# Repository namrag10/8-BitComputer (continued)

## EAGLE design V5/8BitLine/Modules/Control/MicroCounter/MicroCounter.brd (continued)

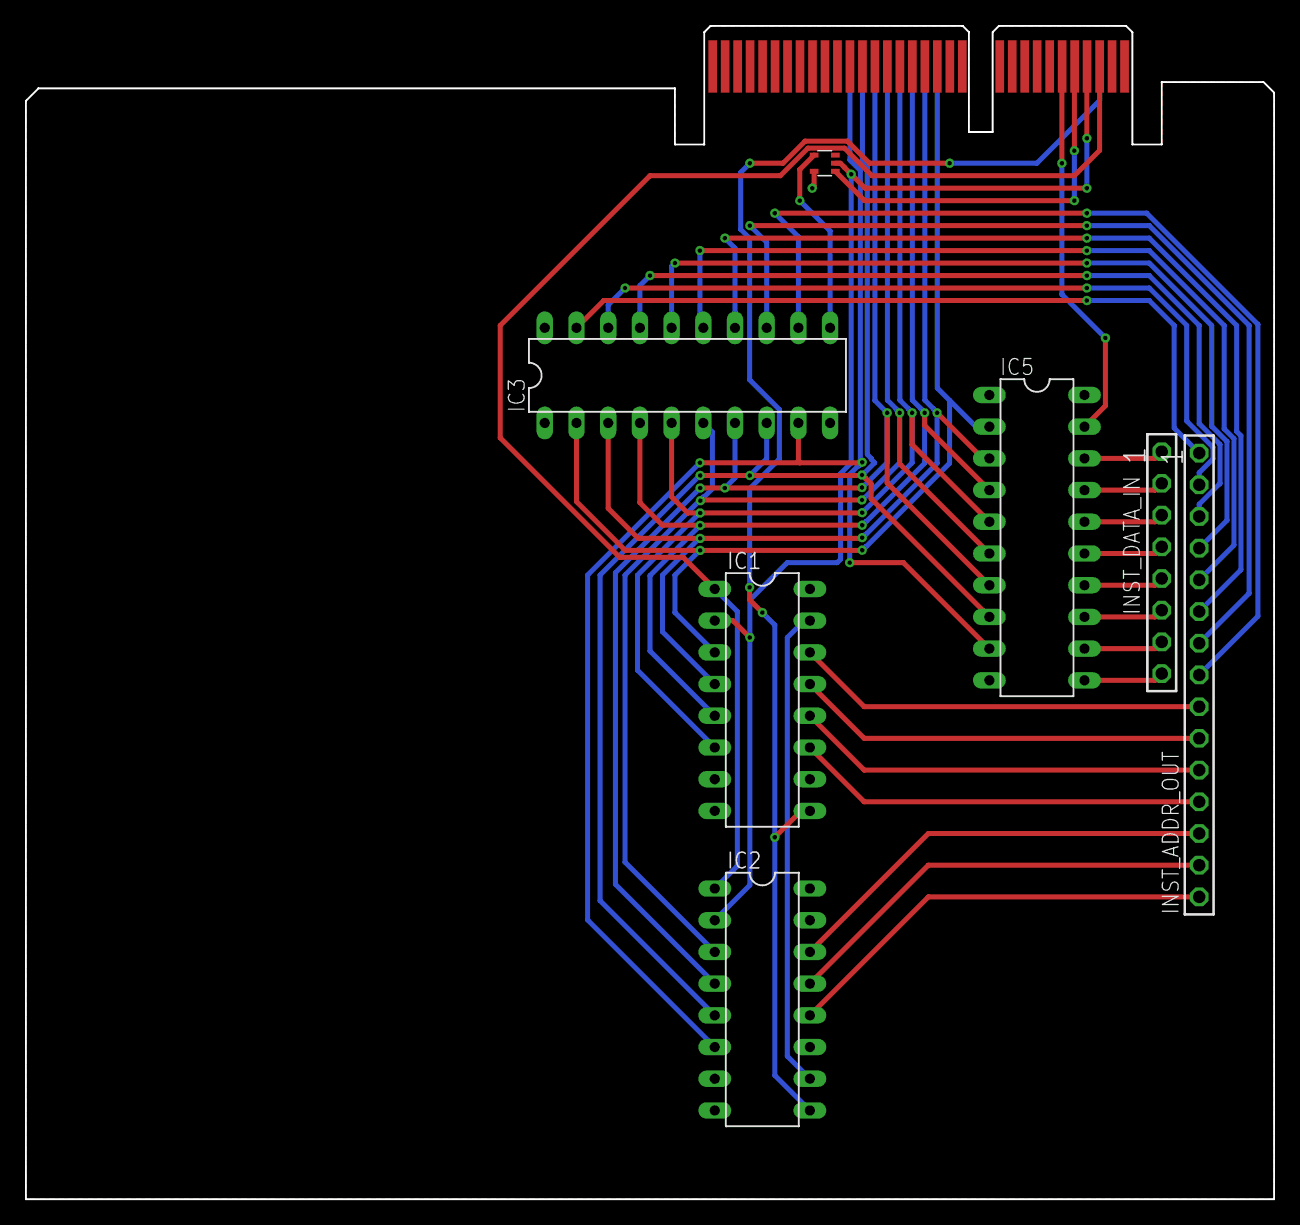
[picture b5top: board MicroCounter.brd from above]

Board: 2 copper layers, 100.0 x 94.0 mm, 8 parts (0 on the bottom side), 40 nets.

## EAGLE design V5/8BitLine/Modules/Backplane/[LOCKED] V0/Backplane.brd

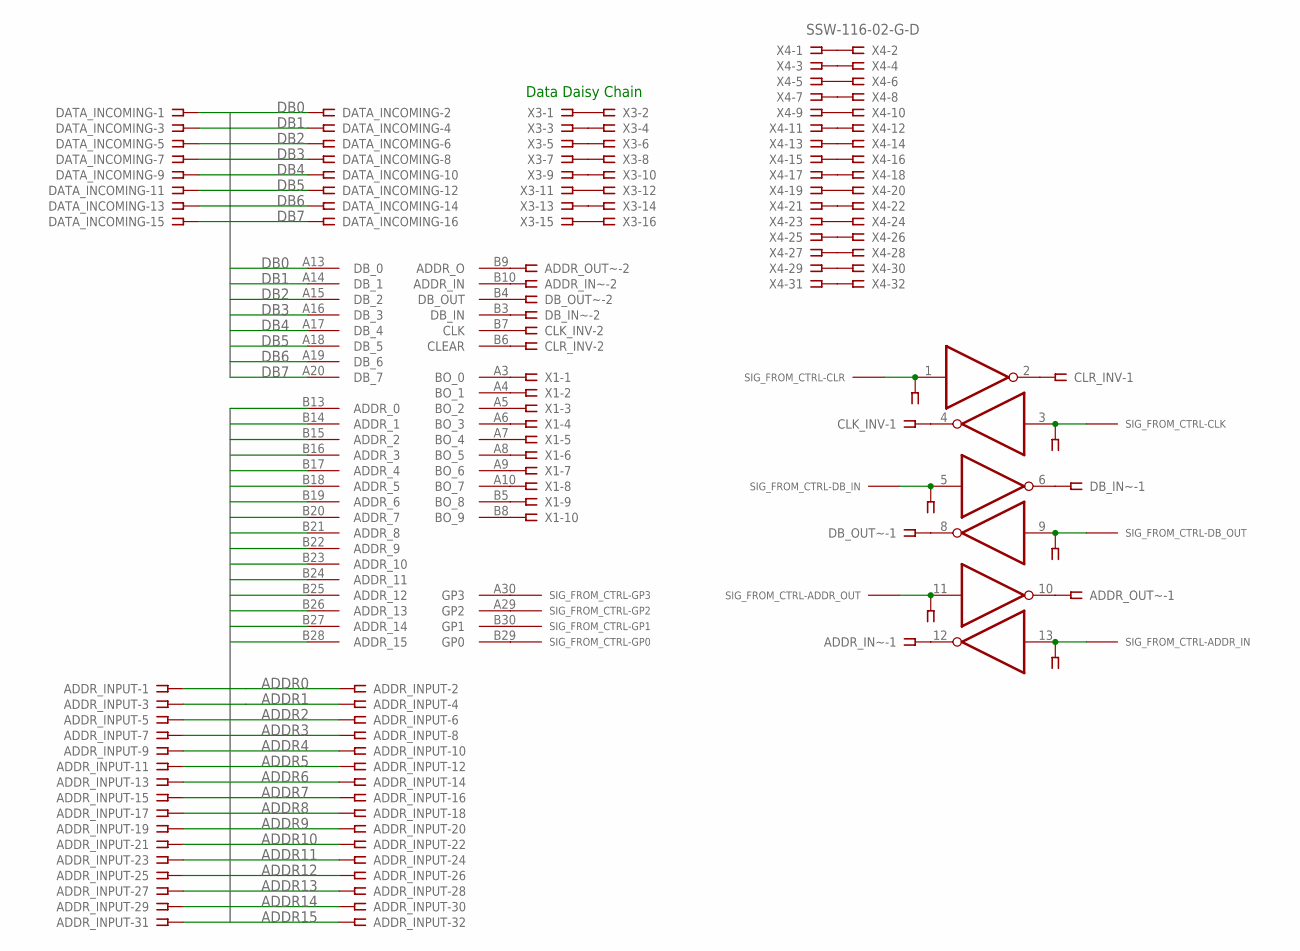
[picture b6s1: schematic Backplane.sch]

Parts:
ADDR_INPUT: SSW-116-02-G-D
ADDR_IN~: SSW-103-02-G-S
ADDR_OUT~: SSW-103-02-G-S
CLK_INV: SSW-103-02-G-S
CLR_INV: SSW-103-02-G-S
DATA_INCOMING: SSW-108-02-G-D
DB_IN~: SSW-103-02-G-S
DB_OUT~: SSW-103-02-G-S
IC1: 74AC04N; DIL14
SIG_FROM_CTRL-: CONTROL_SIG-INT; CONTROL_SIG-INT-FOOT
U$2: BACKPLATE_INTERFACEHEADER; PCI_INTERFACE
X1: SSW-105-02-G-D
X3: SSW-108-02-G-D
X4: SSW-116-02-G-D

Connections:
ADDR0: ADDR_INPUT.1, ADDR_INPUT.2, U$2.B13 (ADDR_0)
ADDR1: ADDR_INPUT.3, ADDR_INPUT.4, U$2.B14 (ADDR_1)
ADDR2: ADDR_INPUT.5, ADDR_INPUT.6, U$2.B15 (ADDR_2)
ADDR3: ADDR_INPUT.7, ADDR_INPUT.8, U$2.B16 (ADDR_3)
ADDR4: ADDR_INPUT.9, ADDR_INPUT.10, U$2.B17 (ADDR_4)
ADDR5: ADDR_INPUT.11, ADDR_INPUT.12, U$2.B18 (ADDR_5)
ADDR6: ADDR_INPUT.13, ADDR_INPUT.14, U$2.B19 (ADDR_6)
ADDR7: ADDR_INPUT.15, ADDR_INPUT.16, U$2.B20 (ADDR_7)
ADDR8: ADDR_INPUT.17, ADDR_INPUT.18, U$2.B21 (ADDR_8)
ADDR9: ADDR_INPUT.19, ADDR_INPUT.20, U$2.B22 (ADDR_9)
ADDR10: ADDR_INPUT.21, ADDR_INPUT.22, U$2.B23 (ADDR_10)
ADDR11: ADDR_INPUT.23, ADDR_INPUT.24, U$2.B24 (ADDR_11)
ADDR12: ADDR_INPUT.25, ADDR_INPUT.26, U$2.B25 (ADDR_12)
ADDR13: ADDR_INPUT.27, ADDR_INPUT.28, U$2.B26 (ADDR_13)
ADDR14: ADDR_INPUT.29, ADDR_INPUT.30, U$2.B27 (ADDR_14)
ADDR15: ADDR_INPUT.31, ADDR_INPUT.32, U$2.B28 (ADDR_15)
DB0: DATA_INCOMING.1, DATA_INCOMING.2, U$2.A13 (DB_0)
DB1: DATA_INCOMING.3, DATA_INCOMING.4, U$2.A14 (DB_1)
DB2: DATA_INCOMING.5, DATA_INCOMING.6, U$2.A15 (DB_2)
DB3: DATA_INCOMING.7, DATA_INCOMING.8, U$2.A16 (DB_3)
DB4: DATA_INCOMING.9, DATA_INCOMING.10, U$2.A17 (DB_4)
DB5: DATA_INCOMING.11, DATA_INCOMING.12, U$2.A18 (DB_5)
DB6: DATA_INCOMING.13, DATA_INCOMING.14, U$2.A19 (DB_6)
DB7: DATA_INCOMING.15, DATA_INCOMING.16, U$2.A20 (DB_7)
GND: IC1.7 (GND), SIG_FROM_CTRL-.GND, U$2.B2 (GND), U$2.B31 (GND)
unnamed: CLR_INV.2, U$2.B6 (CLEAR)
unnamed: CLR_INV.3, IC1.1 (I), SIG_FROM_CTRL-.CLR (0)
unnamed: CLK_INV.2, U$2.B7 (CLK)
unnamed: DB_IN~.2, U$2.B3 (DB_IN)
unnamed: DB_OUT~.2, U$2.B4 (DB_OUT)
unnamed: SIG_FROM_CTRL-.GP0 (0), U$2.B29 (GP0)
unnamed: SIG_FROM_CTRL-.GP1 (0), U$2.B30 (GP1)
unnamed: CLK_INV.3, IC1.3 (I), SIG_FROM_CTRL-.CLK (0)
unnamed: DB_IN~.3, IC1.5 (I), SIG_FROM_CTRL-.DB_IN (0)
unnamed: DB_OUT~.3, IC1.9 (I), SIG_FROM_CTRL-.DB_OUT (0)
unnamed: SIG_FROM_CTRL-.GP2 (0), U$2.A29 (GP2)
unnamed: SIG_FROM_CTRL-.GP3 (0), U$2.A30 (GP3)
unnamed: ADDR_OUT~.3, IC1.11 (I), SIG_FROM_CTRL-.ADDR_OT (0)
unnamed: ADDR_OUT~.1, IC1.10 (O)
unnamed: CLR_INV.1, IC1.2 (O)
unnamed: CLK_INV.1, IC1.4 (O)
unnamed: DB_IN~.1, IC1.6 (O)
unnamed: DB_OUT~.1, IC1.8 (O)
unnamed: ADDR_IN~.3, IC1.13 (I), SIG_FROM_CTRL-.ADDR_IN (0)
unnamed: ADDR_IN~.1, IC1.12 (O)
unnamed: ADDR_OUT~.2, U$2.B9 (ADDR_O)
unnamed: ADDR_IN~.2, U$2.B10 (ADDR_IN)
unnamed: U$2.A3 (BO_0), X1.1
unnamed: U$2.A4 (BO_1), X1.2
unnamed: U$2.A5 (BO_2), X1.3
unnamed: U$2.A6 (BO_3), X1.4
unnamed: U$2.A7 (BO_4), X1.5
unnamed: U$2.A8 (BO_5), X1.6
unnamed: U$2.A9 (BO_6), X1.7
unnamed: U$2.A10 (BO_7), X1.8
unnamed: U$2.B5 (BO_8), X1.9
unnamed: U$2.B8 (BO_9), X1.10
unnamed: X3.1, X3.2
unnamed: X3.3, X3.4
unnamed: X3.5, X3.6
unnamed: X3.7, X3.8
unnamed: X3.9, X3.10
unnamed: X3.11, X3.12
unnamed: X3.13, X3.14
unnamed: X3.15, X3.16
unnamed: X4.1, X4.2
unnamed: X4.3, X4.4
unnamed: X4.5, X4.6
unnamed: X4.7, X4.8
unnamed: X4.9, X4.10
unnamed: X4.11, X4.12
unnamed: X4.13, X4.14
unnamed: X4.15, X4.16
unnamed: X4.17, X4.18
unnamed: X4.19, X4.20
unnamed: X4.21, X4.22
unnamed: X4.23, X4.24
unnamed: X4.25, X4.26
unnamed: X4.27, X4.28
unnamed: X4.29, X4.30
unnamed: X4.31, X4.32
VCC: IC1.14 (VCC), SIG_FROM_CTRL-.VCC, U$2.A2 (VCC), U$2.A31 (VCC)

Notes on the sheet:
Data Daisy Chain

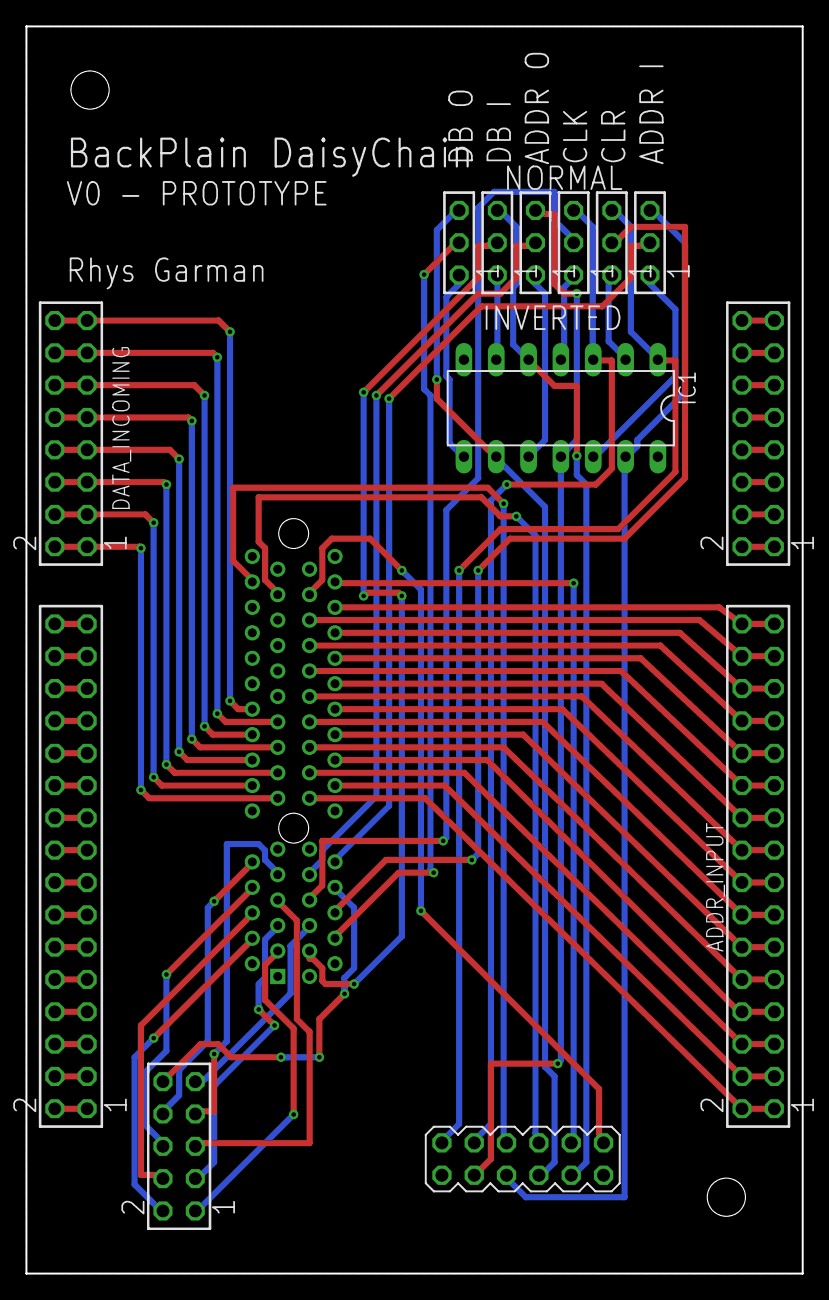
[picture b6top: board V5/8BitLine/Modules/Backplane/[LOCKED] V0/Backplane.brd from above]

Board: 2 copper layers, 61.0 x 98.0 mm, 14 parts (0 on the bottom side), 82 nets.

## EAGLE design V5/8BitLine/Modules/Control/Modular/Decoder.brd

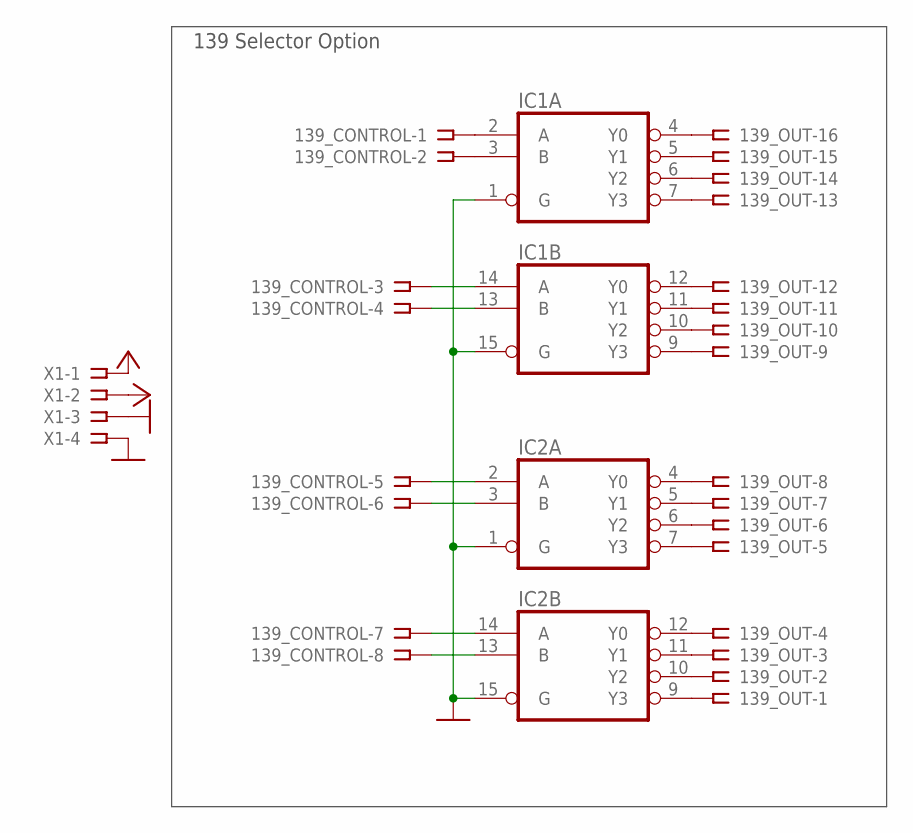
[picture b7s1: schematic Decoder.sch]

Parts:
139_CONTROL: SSW-108-02-G-S
139_OUT: SSW-116-02-G-S
IC1, IC2: 74AC139N; DIL16
X1: SSW-104-02-G-S

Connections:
GND: IC1.1 (G), IC1.8 (GND), IC1.15 (G), IC2.1 (G), IC2.8 (GND), IC2.15 (G), X1.3, X1.4
unnamed: 139_OUT.13, IC1.7 (Y3)
unnamed: 139_OUT.14, IC1.6 (Y2)
unnamed: 139_OUT.15, IC1.5 (Y1)
unnamed: 139_OUT.16, IC1.4 (Y0)
unnamed: 139_OUT.9, IC1.9 (Y3)
unnamed: 139_OUT.10, IC1.10 (Y2)
unnamed: 139_OUT.11, IC1.11 (Y1)
unnamed: 139_OUT.12, IC1.12 (Y0)
unnamed: 139_OUT.5, IC2.7 (Y3)
unnamed: 139_OUT.6, IC2.6 (Y2)
unnamed: 139_OUT.7, IC2.5 (Y1)
unnamed: 139_OUT.8, IC2.4 (Y0)
unnamed: 139_OUT.1, IC2.9 (Y3)
unnamed: 139_OUT.2, IC2.10 (Y2)
unnamed: 139_OUT.3, IC2.11 (Y1)
unnamed: 139_OUT.4, IC2.12 (Y0)
unnamed: 139_CONTROL.1, IC1.2 (A)
unnamed: 139_CONTROL.2, IC1.3 (B)
unnamed: 139_CONTROL.8, IC2.13 (B)
unnamed: 139_CONTROL.7, IC2.14 (A)
unnamed: 139_CONTROL.6, IC2.3 (B)
unnamed: 139_CONTROL.5, IC2.2 (A)
unnamed: 139_CONTROL.4, IC1.13 (B)
unnamed: 139_CONTROL.3, IC1.14 (A)
VCC: IC1.16 (VCC), IC2.16 (VCC), X1.1, X1.2

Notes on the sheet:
139 Selector Option

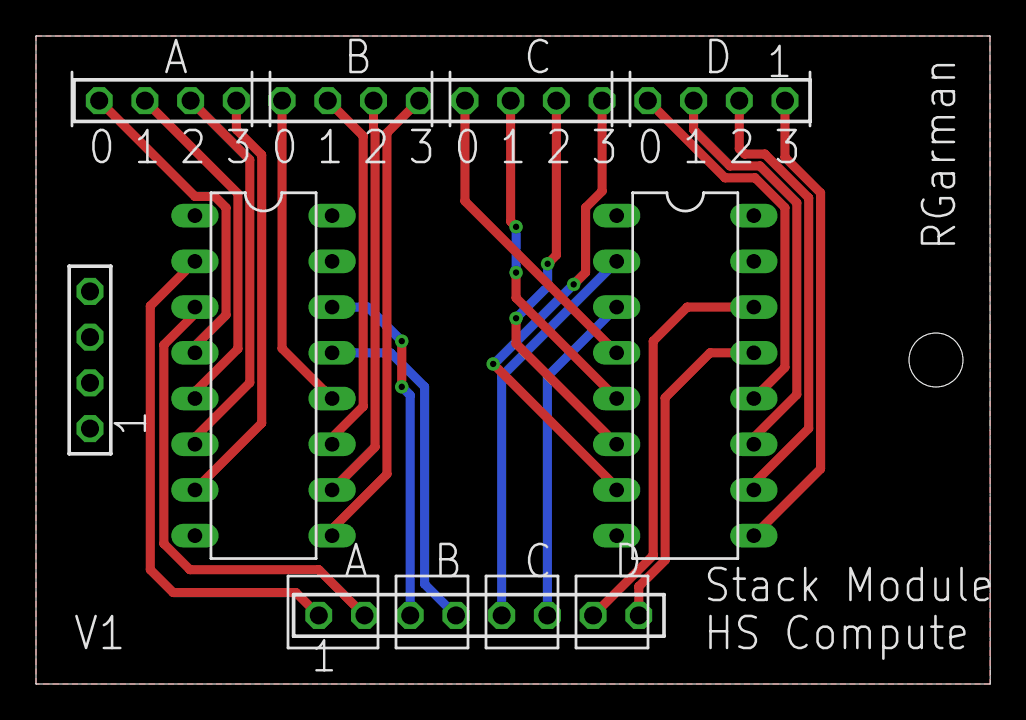
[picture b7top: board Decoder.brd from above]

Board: 2 copper layers, 53.0 x 36.0 mm, 5 parts (0 on the bottom side), 26 nets.

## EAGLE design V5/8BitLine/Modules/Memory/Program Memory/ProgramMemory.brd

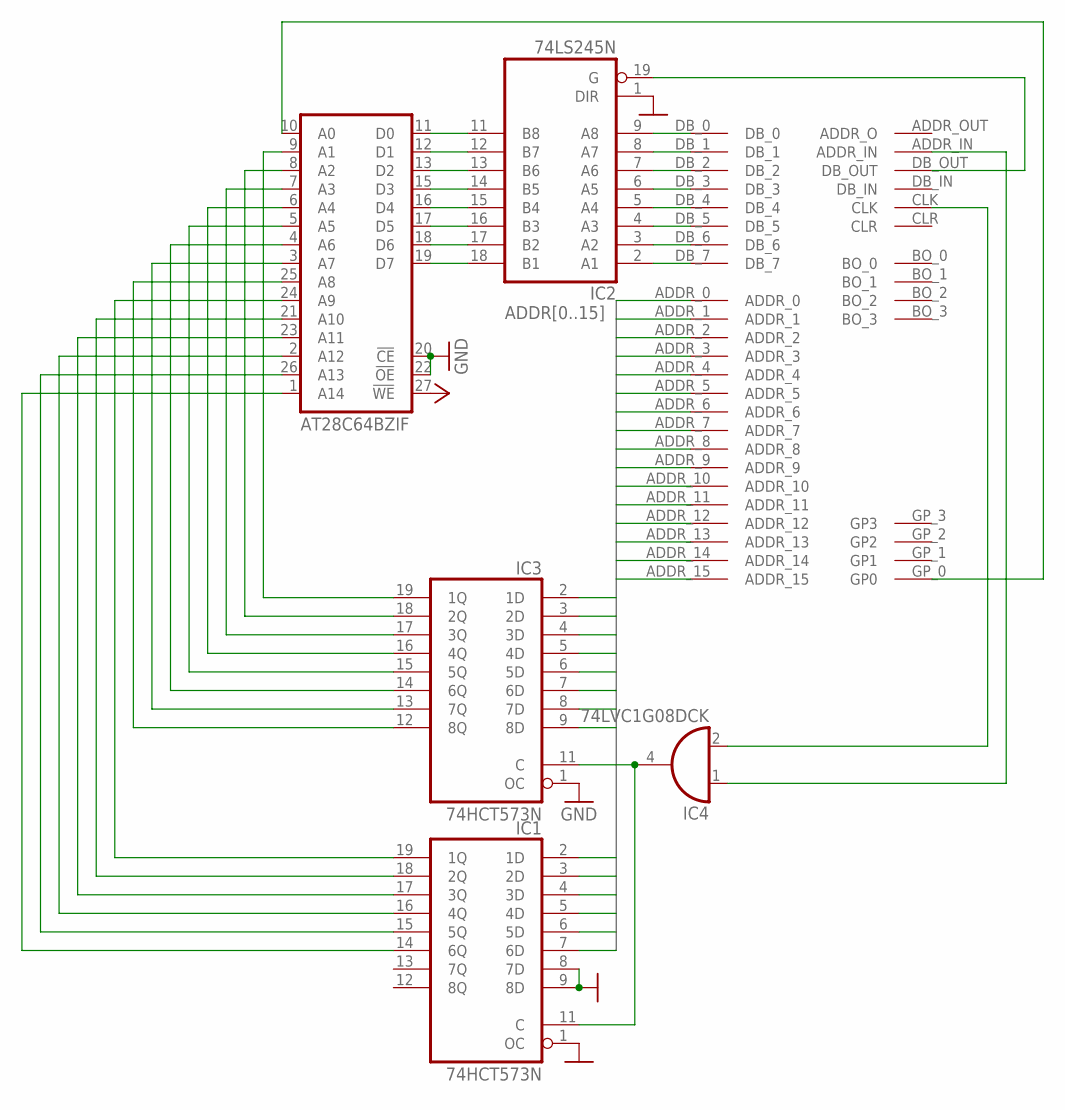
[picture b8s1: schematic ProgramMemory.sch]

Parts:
IC1, IC3: 74HCT573N; DIL20
IC2: 74LS245N; DIL20
IC4: 74LVC1G08DCK; SC70-5
U$1: BACKPLATE_INTERFACEEDGE_FINGER; BACK_INTERFACE-FOOT
U$2: AT28C64BZIF; 28-WIDE_ZIF-FOOT

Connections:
ADDR0: IC3.2 (1D), U$1.ADDR_0
ADDR1: IC3.3 (2D), U$1.ADDR_1
ADDR2: IC3.4 (3D), U$1.ADDR_2
ADDR3: IC3.5 (4D), U$1.ADDR_3
ADDR4: IC3.6 (5D), U$1.ADDR_4
ADDR5: IC3.7 (6D), U$1.ADDR_5
ADDR6: IC3.8 (7D), U$1.ADDR_6
ADDR7: IC3.9 (8D), U$1.ADDR_7
ADDR8: IC1.2 (1D), U$1.ADDR_8
ADDR9: IC1.3 (2D), U$1.ADDR_9
ADDR10: IC1.4 (3D), U$1.ADDR_10
ADDR11: IC1.5 (4D), U$1.ADDR_11
ADDR12: IC1.6 (5D), U$1.ADDR_12
ADDR13: IC1.7 (6D), U$1.ADDR_13
ADDR14: U$1.ADDR_14
ADDR15: U$1.ADDR_15
DATA0: IC2.9 (A8), U$1.DB_0
DATA1: IC2.8 (A7), U$1.DB_1
DATA2: IC2.7 (A6), U$1.DB_2
DATA3: IC2.6 (A5), U$1.DB_3
DATA4: IC2.5 (A4), U$1.DB_4
DATA5: IC2.4 (A3), U$1.DB_5
DATA6: IC2.3 (A2), U$1.DB_6
DATA7: IC2.2 (A1), U$1.DB_7
GND: IC1.1 (OC), IC1.8 (7D), IC1.9 (8D), IC1.10 (GND), IC2.1 (DIR), IC2.10 (GND), IC3.1 (OC), IC3.10 (GND), IC4.3 (GND), U$1.GND_0 (GND), U$1.GND_1 (GND), U$2.14 (GND), U$2.20 (!CE), U$2.22 (!OE)
unnamed: U$1.GP_0 (GP0), U$2.10 (A0)
unnamed: IC3.19 (1Q), U$2.9 (A1)
unnamed: IC3.18 (2Q), U$2.8 (A2)
unnamed: IC3.17 (3Q), U$2.7 (A3)
unnamed: IC3.16 (4Q), U$2.6 (A4)
unnamed: IC3.15 (5Q), U$2.5 (A5)
unnamed: IC3.14 (6Q), U$2.4 (A6)
unnamed: IC3.13 (7Q), U$2.3 (A7)
unnamed: IC3.12 (8Q), U$2.25 (A8)
unnamed: IC1.19 (1Q), U$2.24 (A9)
unnamed: IC1.18 (2Q), U$2.21 (A10)
unnamed: IC1.17 (3Q), U$2.23 (A11)
unnamed: IC1.16 (4Q), U$2.2 (A12)
unnamed: IC1.15 (5Q), U$2.26 (A13)
unnamed: IC1.14 (6Q), U$2.1 (A14)
unnamed: IC1.11 (C), IC3.11 (C), IC4.4 (O)
unnamed: IC4.2 (I1), U$1.CLK
unnamed: IC4.1 (I0), U$1.ADDR_IN
unnamed: IC2.19 (G), U$1.DB_OUT
RS_BREAKOUT0: IC2.11 (B8), U$2.11 (D0)
RS_BREAKOUT1: IC2.12 (B7), U$2.12 (D1)
RS_BREAKOUT2: IC2.13 (B6), U$2.13 (D2)
RS_BREAKOUT3: IC2.14 (B5), U$2.15 (D3)
RS_BREAKOUT4: IC2.15 (B4), U$2.16 (D4)
RS_BREAKOUT5: IC2.16 (B3), U$2.17 (D5)
RS_BREAKOUT6: IC2.17 (B2), U$2.18 (D6)
RS_BREAKOUT7: IC2.18 (B1), U$2.19 (D7)
VCC: IC1.20 (VCC), IC2.20 (VCC), IC3.20 (VCC), IC4.5 (VCC), U$1.VCC_0 (VCC), U$1.VCC_1 (VCC), U$2.27 (!WE), U$2.28 (VCC)

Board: 2 copper layers, 6 parts (0 on the bottom side), 51 nets, no tracks yet.

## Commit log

2021-12-25 Commit xD
2021-12-25 Tidy and added Instructions
2021-12-28 Updated spreadsheet and overwritten XOR gate for overflow on subtract
2022-02-02 Added Instructions
2022-02-02 Added gitignore
2022-02-03 Added Programmer and breadboard version
2022-02-11 Update lmao
2022-05-13 efficiency upgrade
2022-07-06 Added Ignore
